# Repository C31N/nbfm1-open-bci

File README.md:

<!-- SPDX-License-Identifier: AGPL-3.0-only -->
# NBFM-1 Open BCI Stack

\n

Open-source research platform for a multimodal, non-invasive brain-computer interface built around three independently useful layers:

1. **NBFM-1** — an asynchronous neural foundation model with a millisecond-scale EEG/MEG fast path and a slower fNIRS context path.
2. **P1/P2 edge stack** — local inference, TensorRT/ONNX deployment, CUDA Graph-compatible I/O, encrypted local transport, intent gating, privacy zeroization, telemetry and systemd services.
3. **EEG128-TDM** — an ultra-low-cost 128-channel differential EEG acquisition architecture using paired 16:1 analog multiplexers, an 8-channel simultaneous-sampling delta-sigma ADC and an RP2040-class controller.

> **Research use only.** This repository does not claim medical-device certification, diagnostic suitability, prosthesis safety certification or validated free-form thought decoding. The project owner reports an existing external demonstration of multimodal measurement latency below 5 ms. The external report's raw samples and measurement conditions have not been imported into this checkout; preserve its actual measurement boundary when incorporating it. See [measurement scope and executable reference pipeline](docs/NEURAL_PIPELINE.md).

## Defensive publication

The enabling technical disclosure is in [`PATENT_DISCLOSURE.md`](PATENT_DISCLOSURE.md). The document is intentionally explicit about timing, packet formats, signal routing, filter-settling handling, asynchronous multimodal fusion and privacy gating so the disclosed combinations can be independently implemented and searched as public technical literature.

A repository commit is evidence, not magic. For a stronger publication record, publish a signed release, generate the repository SHA-256 manifest and archive that release in a DOI-backed repository such as Zenodo. See [`docs/PUBLICATION_PROCEDURE.md`](docs/PUBLICATION_PROCEDURE.md).

## System architecture

```mermaid
flowchart LR
    EEG["128-ch EEG<br/>1 kHz after decimation"] --> FAST["Fast neural path"]
    MEG["OPM-MEG<br/>geometry embeddings"] --> FAST
    FNIRS["fNIRS<br/>20 Hz short/long separation"] --> SLOW["Slow context encoder"]
    FAST --> NBFM["NBFM-1 causal transformer"]
    SLOW --> XATTN["Cross-attention"]
    XATTN --> NBFM
    NBFM --> MOTOR["Motor Gaussian head<br/>mu + sigma"]
    NBFM --> GATE["Intent gate<br/>P(intent)"]
    NBFM --> CTC["Phonemic CTC head"]
    GATE --> PRIVACY["Local-first privacy gate"]
    CTC --> PRIVACY
    PRIVACY --> ENC["AES-256-GCM local export"]
    MOTOR --> SAFETY["Rate/uncertainty limiter"]
    ENC --> AGENT["Local agent adapter"]
    SAFETY --> ACT["Cursor / bench actuator interface"]
```

### EEG128-TDM acquisition path

```mermaid
flowchart LR
    E["128 differential EEG channels<br/>256 electrode conductors"] --> M["8 banks x paired 16:1 MUX<br/>16 CD74HC4067 total"]
    M --> B["16 low-noise unity buffers"]
    B --> A["ADS131M08<br/>8 simultaneous 24-bit delta-sigma channels<br/>32 kSPS"]
    A --> R["RP2040<br/>SPI + DMA"]
    R --> D["16-position demultiplex<br/>settling discard + averaging"]
    D --> O["128 channels x 250 SPS<br/>offset/gain correction"]
```

## Hardware revision status

The repository contains **EEG128-TDM Revision A0** KiCad/BOM/CPL/netlist sources, but A0 is **not released for fabrication or human-connected use**. The board still requires independent routing and footprint verification followed by clean KiCad 8 ERC/DRC and the safety release gates in [`docs/SAFETY_COMPLIANCE.md`](docs/SAFETY_COMPLIANCE.md).

The manufacturing exporter is fail-closed: [`hardware/eeg128-tdm/generate_manufacturing.py`](hardware/eeg128-tdm/generate_manufacturing.py) refuses to generate Gerber output while [`RELEASE_STATUS.json`](hardware/eeg128-tdm/RELEASE_STATUS.json) contains an unmet release gate.

## Privacy-state machine

```text
LOCKED --explicit local arm--> ARMED --P(intent) >= T_gate--> DECODING
   ^                          |                              |
   |                          +--below threshold------------+
   +---------------- timeout / lock / fault ----------------+
```

Speech logits remain local. When the gate is closed, the export tensor is replaced with a fixed-shape zero tensor before encryption. Frame dimensions therefore do not reveal whether a private speech hypothesis existed.

## Physical hardware release status

The repository contains the A0 KiCad project, logical netlist, BOM/CPL and fail-closed manufacturing tooling, but **A0 is not released for fabrication or human-connected use**.

The current audited EDA state has placement/net assignments but not completed copper routing, and the current schematic is a connectivity index rather than a complete instantiated circuit schematic. The authoritative release blockers are machine-readable in `hardware/eeg128-tdm/RELEASE_STATUS.json`.

Run:

```bash
python3 hardware/eeg128-tdm/validate_eda.py
```

Manufacturing export remains blocked until the independent physical release gates are satisfied.

See:

- `hardware/eeg128-tdm/EDA_AUDIT.md`
- `docs/SAFETY_COMPLIANCE.md`
- `docs/AUDIT_2026-10-05.md`

## Quick start

```bash
chmod +x deploy_bci_stack.sh
./deploy_bci_stack.sh
```

Run the latency auditor after inference and bridge services are healthy:

```bash
python3 bin/audit_latency.py \
  --json reports/latency-audit.json \
  --html reports/latency-audit.html
```

A new benchmark passes only when its measured P99 meets the configured threshold.
The external result reported by the owner and a new revision's local compute
benchmark have separate evidence records. `bin/verify_latency_evidence.py` can
recompute an imported report without changing its stated measurement boundary.

The [reference pipeline guide](docs/NEURAL_PIPELINE.md) includes native LSL
ingestion, Python/Rust bounded rings, causal filtering, MAE/ridge interfaces and
AES-256-GCM session handling. The [143-airwire routing plan](hardware/eeg128-tdm/ROUTING_COMPLETION_143.md)
defines the remaining hardware work and the manufacturing prohibition.

## Licensing

Hardware design source and firmware are licensed under **CERN Open Hardware Licence Version 2 — Strongly Reciprocal (`CERN-OHL-S-2.0`)**. The NBFM-1 software architecture, inference stack, privacy gate, deployment code, scripts and project documentation are licensed under **GNU Affero General Public License v3.0 only (`AGPL-3.0-only`)**.

## Citation

Machine-readable citation metadata is in [`CITATION.cff`](CITATION.cff).

## Security

Neural raw data, derived embeddings, decoded speech, session keys, model weights and device-specific calibration can be sensitive. Never commit them. See [`SECURITY.md`](SECURITY.md) and the enforced exclusions in [`.gitignore`](.gitignore).

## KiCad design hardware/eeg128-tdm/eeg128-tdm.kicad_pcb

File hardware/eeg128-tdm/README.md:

<!-- SPDX-License-Identifier: CERN-OHL-S-2.0 -->
# EEG128-TDM Hardware Source — Revision A0

## Architecture

```text
128 differential logical EEG channels
= 256 subject/electrode conductors
        |
        v
8 banks x 16 logical channels
        |
        v
16 paired CD74HC4067-class 16:1 multiplexers
        |
        v
16 TLV9064-class unity buffers
        |
        v
ADS131M08-class 8-channel simultaneous delta-sigma ADC
32 kSPS, external 8.192-MHz clock
        |
        v
RP2040 SPI1 + DMA
        |
        v
4 post-switch conversions discarded
4 late conversions averaged
        |
        v
128 logical channels x 250 SPS
```

## Source files

| File | Purpose |
|---|---|
| `design_spec.yaml` | Human-readable electrical/stack-up source of truth |
| `NETLIST.csv` | Detailed endpoint-to-endpoint logical connectivity |
| `BOM.csv` | JLCPCB/LCSC-oriented bill of materials |
| `CPL.csv` | JLCPCB-oriented component placement |
| `eeg128-tdm.kicad_sch` | KiCad 8 schematic/connectivity index |
| `generate_schematic.py` | Deterministically generates a 642-component KiCad connectivity schematic from PCB pad/net assignments |
| `eeg128-tdm.kicad_pcb` | KiCad 8 four-layer A0 placement/net board |
| `eeg128-tdm.kicad_pro` | KiCad project |
| `validate_eda.py` | Source/BOM/CPL/net validation |
| `generate_manufacturing.py` | Fail-closed KiCad 8 ERC/DRC/Gerber/JLCPCB export |
| `RELEASE_STATUS.json` | Machine-readable fabrication/human-use release gates |

## Current fabrication status

**Revision A0 is not released for fabrication.**

The board source currently contains 642 component placements and logical pad-to-net assignments for A0 design review, but the copper routing is not complete, the KiCad schematic remains a generated connectivity representation rather than a manufacturer-symbol/pin-type reviewed circuit schematic, and generated footprint land patterns have not been independently verified. `RELEASE_STATUS.json` therefore keeps `fabrication_release=false`.

This is intentional. A large human-connected mixed-signal board must not become orderable merely because source files exist.

The manufacturing exporter refuses to run until all release gates are true.

## Validation

Repository-level structural validation:

```bash
python3 hardware/eeg128-tdm/validate_eda.py
```

Release validation additionally requires KiCad CLI 8:

```bash
cd hardware/eeg128-tdm
python3 validate_eda.py --kicad-release-checks
```

After independent routing/footprint/safety review and only after `RELEASE_STATUS.json` is intentionally signed off:

```bash
python3 generate_manufacturing.py
```

The script executes KiCad ERC and PCB DRC before exporting Gerber, drill and position data. Any failed release gate or KiCad violation stops the export.

## Four-layer intent

```text
L1  F.Cu   analog inputs, MUX/buffer/ADC and short local digital routes
L2  In1.Cu continuous return plane; analog/digital domains managed by placement/current paths
L3  In2.Cu 3V3A / 3V3D / VCM distribution
L4  B.Cu   high-speed digital, USB and controller-side routing
```

Do not create arbitrary AGND/DGND moat cuts that force return currents to detour. Domain control is primarily by placement/routing, with the ground-domain connection deliberately reviewed at the ADC/power boundary.

## Safety

This is research hardware, not IEC 60601-certified equipment.

No human-connected use is authorized by this repository revision. Follow `docs/SAFETY_COMPLIANCE.md`. In particular, a subject-connected analog domain must not have an uncontrolled galvanic path to mains-referenced equipment.

## License

Hardware source is covered by `CERN-OHL-S-2.0`.

## Package and grounding audit

### ADS131M08IPBSR

Use the TI **PBS** mechanical drawing as the authoritative footprint reference. The package has a nominal 5 mm square body with 0.50 mm lead pitch and approximately 7 mm overall lead span. Distributor summaries can describe these dimensions differently; release review must use the manufacturer drawing.

### Ground plane

The current logical source uses separate `AGND` and `DGND` names while the intended PCB strategy calls for a continuous return plane. This conflict must be resolved before routing release. Do not introduce an arbitrary split-plane slot solely to preserve naming.

### Internal reference

The selected low-noise reference network must be reviewed explicitly before A0 fabrication. The present logical netlist records `ADC_REFIN` as unpopulated; for EEG noise optimization, provision for local REFIN filtering must be evaluated against TI guidance and the chosen converter mode.

See `EDA_AUDIT.md` and `RELEASE_STATUS.json`.

## Generated connectivity schematic

The deterministic generator can materialize every PCB/BOM component and every assigned pad net into a KiCad 8 schematic representation:

```bash
python3 generate_schematic.py
```

Default output:

```text
eeg128-tdm.generated.kicad_sch
```

It uses real component references and PCB pad numbers and emits local labeled wire stubs for assigned nets. It intentionally uses conservative generic passive-pin symbols. Therefore it is useful for reproducible connectivity review and schematic/PCB parity, but it does **not** replace manufacturer-symbol pin-type review, analog/power/reference design review, or independently establish fabrication readiness.

Only after review may it replace the primary schematic:

```bash
python3 generate_schematic.py --replace-primary
```

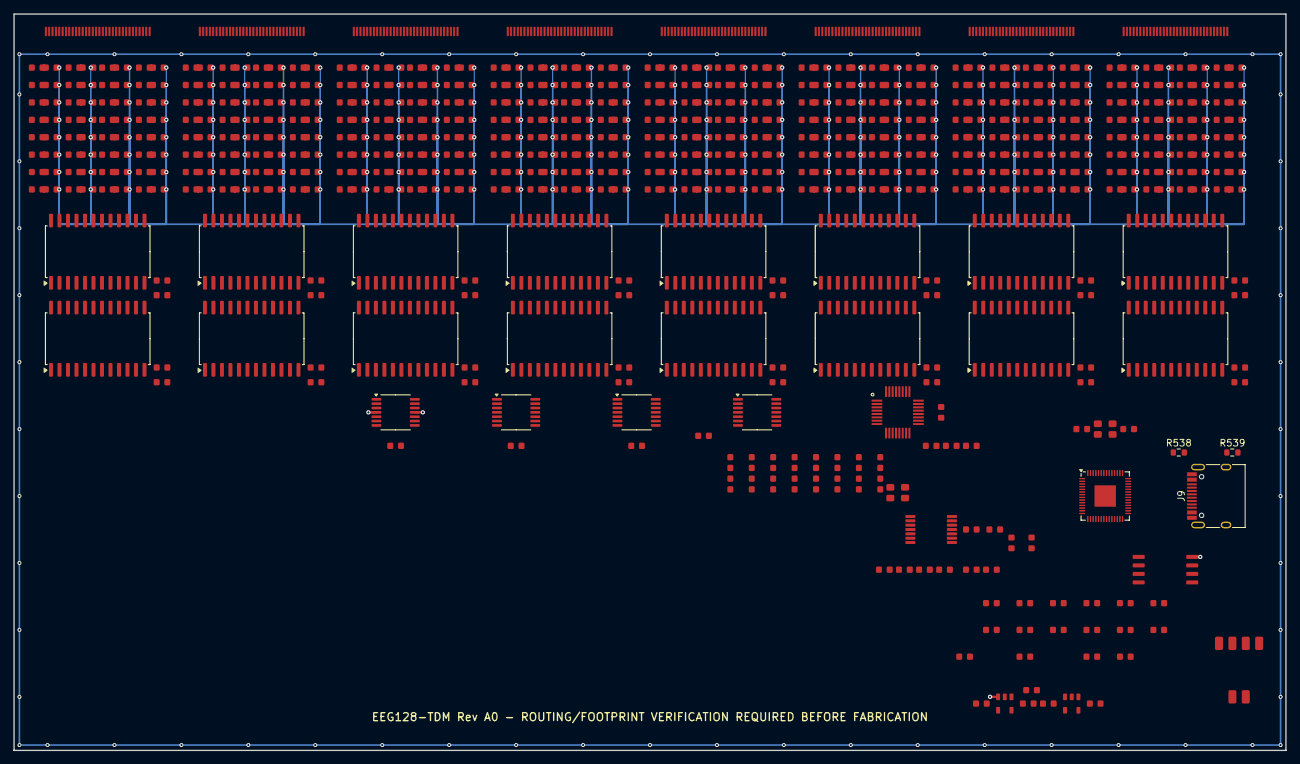
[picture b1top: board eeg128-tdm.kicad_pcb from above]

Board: 4 copper layers, 190.0 x 110.0 mm, 642 parts (0 on the bottom side), 604 nets.

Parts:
C1: C1
C2: C2
C3: C3
C4: C4
C5: C5
C6: C6
C7: C7
C8: C8
C9: C9
C10: C10
C11: C11
C12: C12
C13: C13
C14: C14
C15: C15
C16: C16
C17: C17
C18: C18
C19: C19
C20: C20
C21: C21
C22: C22
C23: C23
C24: C24
C25: C25
C26: C26
C27: C27
C28: C28
C29: C29
C30: C30
C31: C31
C32: C32
C33: C33
C34: C34
C35: C35
C36: C36
C37: C37
C38: C38
C39: C39
C40: C40
C41: C41
C42: C42
C43: C43
C44: C44
C45: C45
C46: C46
C47: C47
C48: C48
C49: C49
C50: C50
C51: C51
C52: C52
C53: C53
C54: C54
C55: C55
C56: C56
C57: C57
C58: C58
C59: C59
C60: C60
C61: C61
C62: C62
C63: C63
C64: C64
J1: J1
J2: J2
J3: J3
J4: J4
J5: J5
J6: J6
J7: J7
J8: J8
J9: TYPE-C-31-M-12; USB_C_Receptacle_HRO_TYPE-C-31-M-12
J10: J10
J11: J11
R1: R1
R2: R2
R3: R3
R4: R4
R5: R5
R6: R6
R7: R7
R8: R8
R9: R9
R10: R10
R11: R11
R12: R12
R13: R13
R14: R14
R15: R15
R16: R16
R17: R17
R18: R18
R19: R19
R20: R20
R21: R21
R22: R22
R23: R23
R24: R24
R25: R25
R26: R26
R27: R27
R28: R28
R29: R29
R30: R30
R31: R31
R32: R32
R33: R33
R34: R34
R35: R35
R36: R36
R37: R37
R38: R38
R39: R39
R40: R40
R41: R41
R42: R42
R43: R43
R44: R44
R45: R45
R46: R46
R47: R47
R48: R48
R49: R49
R50: R50
R51: R51
R52: R52
R53: R53
R54: R54
R55: R55
R56: R56
R57: R57
R58: R58
R59: R59
R60: R60
R61: R61
R62: R62
R63: R63
R64: R64
R65: R65
R66: R66
R67: R67
R68: R68
R69: R69
R70: R70
R71: R71
R72: R72
R73: R73
R74: R74
R75: R75
R76: R76
R77: R77
R78: R78
R79: R79
R80: R80
R81: R81
R82: R82
R83: R83
R84: R84
R85: R85
R86: R86
R87: R87
R88: R88
R89: R89
R90: R90
R91: R91
R92: R92
R93: R93
R94: R94
R95: R95
R96: R96
R97: R97
R98: R98
R99: R99
R100: R100
R101: R101
R102: R102
R103: R103
R104: R104
R105: R105
R106: R106
R107: R107
R108: R108
R109: R109
R110: R110
R111: R111
R112: R112
R113: R113
R114: R114
R115: R115
R116: R116
R117: R117
R118: R118
R119: R119
R120: R120
R121: R121
R122: R122
R123: R123
R124: R124
R125: R125
R126: R126
R127: R127
R128: R128
R129: R129
R130: R130
R131: R131
R132: R132
R133: R133
R134: R134
R135: R135
R136: R136
R137: R137
R138: R138
R139: R139
R140: R140
R141: R141
R142: R142
R143: R143
R144: R144
R145: R145
R146: R146
R147: R147
R148: R148
R149: R149
R150: R150
R151: R151
R152: R152
R153: R153
R154: R154
R155: R155
R156: R156
R157: R157
R158: R158
R159: R159
R160: R160
R161: R161
R162: R162
R163: R163
R164: R164
R165: R165
R166: R166
R167: R167
R168: R168
R169: R169
R170: R170
R171: R171
R172: R172
R173: R173
R174: R174
R175: R175
R176: R176
R177: R177
R178: R178
R179: R179
R180: R180
R181: R181
R182: R182
R183: R183
R184: R184
R185: R185
R186: R186
R187: R187
R188: R188
R189: R189
R190: R190
R191: R191
R192: R192
R193: R193
R194: R194
R195: R195
R196: R196
R197: R197
R198: R198
R199: R199
R200: R200
R201: R201
R202: R202
R203: R203
R204: R204
R205: R205
R206: R206
R207: R207
R208: R208
R209: R209
R210: R210
R211: R211
R212: R212
R213: R213
R214: R214
R215: R215
R216: R216
R217: R217
R218: R218
R219: R219
R220: R220
R221: R221
R222: R222
R223: R223
R224: R224
R225: R225
R226: R226
R227: R227
R228: R228
R229: R229
R230: R230
R231: R231
R232: R232
R233: R233
R234: R234
R235: R235
R236: R236
R237: R237
R238: R238
R239: R239
R240: R240
R241: R241
R242: R242
R243: R243
R244: R244
R245: R245
R246: R246
R247: R247
R248: R248
R249: R249
R250: R250
R251: R251
R252: R252
R253: R253
R254: R254
R255: R255
R256: R256
R257: R257
R258: R258
R259: R259
R260: R260
R261: R261
R262: R262
R263: R263
R264: R264
R265: R265
R266: R266
R267: R267
R268: R268
R269: R269
R270: R270
R271: R271
R272: R272
R273: R273
R274: R274
R275: R275
R276: R276
R277: R277
R278: R278
R279: R279
R280: R280
R281: R281
R282: R282
R283: R283
R284: R284
R285: R285
R286: R286
R287: R287
R288: R288
R289: R289
R290: R290
R291: R291
R292: R292
R293: R293
R294: R294
R295: R295
R296: R296
R297: R297
R298: R298
R299: R299
R300: R300
R301: R301
R302: R302
R303: R303
R304: R304
R305: R305
R306: R306
R307: R307
R308: R308
R309: R309
R310: R310
R311: R311
R312: R312
R313: R313
R314: R314
R315: R315
R316: R316
R317: R317
R318: R318
R319: R319
R320: R320
R321: R321
R322: R322
R323: R323
R324: R324
R325: R325
R326: R326
R327: R327
R328: R328
R329: R329
R330: R330
R331: R331
R332: R332
R333: R333
R334: R334
R335: R335
R336: R336
R337: R337
R338: R338
R339: R339
R340: R340
R341: R341
R342: R342
R343: R343
R344: R344
R345: R345
R346: R346
R347: R347
R348: R348
R349: R349
R350: R350
R351: R351
R352: R352
R353: R353
R354: R354
R355: R355
R356: R356
R357: R357
R358: R358
R359: R359
R360: R360
R361: R361
R362: R362
R363: R363
R364: R364
R365: R365
R366: R366
R367: R367
R368: R368
R369: R369
R370: R370
R371: R371
R372: R372
R373: R373
R374: R374
R375: R375
R376: R376
R377: R377
R378: R378
R379: R379
R380: R380
R381: R381
R382: R382
R383: R383
R384: R384
R385: R385
R386: R386
R387: R387
R388: R388
R389: R389
R390: R390
R391: R391
R392: R392
R393: R393
R394: R394
R395: R395
R396: R396
R397: R397
R398: R398
R399: R399
R400: R400
R401: R401
R402: R402
R403: R403
R404: R404
R405: R405
R406: R406
R407: R407
R408: R408
R409: R409
R410: R410
R411: R411
R412: R412
R413: R413
R414: R414
R415: R415
R416: R416
R417: R417
R418: R418
R419: R419
R420: R420
R421: R421
R422: R422
R423: R423
R424: R424
R425: R425
R426: R426
R427: R427
R428: R428
R429: R429
R430: R430
R431: R431
R432: R432
R433: R433
R434: R434
R435: R435
R436: R436
R437: R437
R438: R438
R439: R439
R440: R440
R441: R441
R442: R442
R443: R443
R444: R444
R445: R445
R446: R446
R447: R447
R448: R448
R449: R449
R450: R450
R451: R451
R452: R452
R453: R453
R454: R454
R455: R455
R456: R456
R457: R457
R458: R458
R459: R459
R460: R460
R461: R461
R462: R462
R463: R463
R464: R464
R465: R465
R466: R466
R467: R467
R468: R468
R469: R469
R470: R470
R471: R471
R472: R472
R473: R473
R474: R474
R475: R475
R476: R476
R477: R477
R478: R478
R479: R479
R480: R480
R481: R481
R482: R482
R483: R483
R484: R484
R485: R485
R486: R486
R487: R487
R488: R488
R489: R489
R490: R490
R491: R491
R492: R492
R493: R493
R494: R494
R495: R495
R496: R496
R497: R497
R498: R498
R499: R499
R500: R500
R501: R501
R502: R502
R503: R503
R504: R504
R505: R505
R506: R506
R507: R507
R508: R508
R509: R509
R510: R510
R511: R511
R512: R512
R513: R513
R514: R514
R515: R515
R516: R516
R517: R517
R518: R518
R519: R519
R520: R520
R521: R521
R522: R522
R523: R523
R524: R524
R525: R525
R526: R526
R527: R527
R528: R528
R529: R529
R530: R530
R531: R531
R532: R532
R533: R533
R534: R534
R535: R535
R536: R536
R537: R537
R538, R539: 5.1k; R_0603_1608Metric
U1: U1; SOIC-24W_7.5x15.4mm_P1.27mm
U2: U2; SOIC-24W_7.5x15.4mm_P1.27mm
U3: U3; SOIC-24W_7.5x15.4mm_P1.27mm
U4: U4; SOIC-24W_7.5x15.4mm_P1.27mm
U5: U5; SOIC-24W_7.5x15.4mm_P1.27mm
U6: U6; SOIC-24W_7.5x15.4mm_P1.27mm
U7: U7; SOIC-24W_7.5x15.4mm_P1.27mm
U8: U8; SOIC-24W_7.5x15.4mm_P1.27mm
U9: U9; SOIC-24W_7.5x15.4mm_P1.27mm
U10: U10; SOIC-24W_7.5x15.4mm_P1.27mm
U11: U11; SOIC-24W_7.5x15.4mm_P1.27mm
U12: U12; SOIC-24W_7.5x15.4mm_P1.27mm
U13: U13; SOIC-24W_7.5x15.4mm_P1.27mm
U14: U14; SOIC-24W_7.5x15.4mm_P1.27mm
U15: U15; SOIC-24W_7.5x15.4mm_P1.27mm
U16: U16; SOIC-24W_7.5x15.4mm_P1.27mm
U17: U17; TSSOP-14_4.4x5mm_P0.65mm
U18: U18; TSSOP-14_4.4x5mm_P0.65mm
U19: U19; TSSOP-14_4.4x5mm_P0.65mm
U20: U20; TSSOP-14_4.4x5mm_P0.65mm
U21: U21; TI_PBS_S-PQFP-G32_5x5mm_P0.5mm
U22: U22
U23: U23; QFN-56-1EP_7x7mm_P0.4mm_EP3.2x3.2mm
U24: U24
U25: U25
U26: U26
U27: U27
Y1: Y1

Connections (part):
3V3A: C1.1, C2.1, C3.1, C4.1, C5.1, C6.1, C7.1, C8.1, C9.1, C10.1, C11.1, C12.1, C13.1, C14.1, C15.1, C16.1, C18.1, C21.1, C22.1, C23.1, C24.1, C25.1, C26.1, C27.1, C28.1, C29.1, C30.1, C31.1, C32.1, C33.1, C34.1, C35.1, C36.1, C37.1, C38.1, C39.1, C40.1, C41.1, R529.1, U1.24, U2.24, U3.24, U4.24, U5.24, U6.24, U7.24, U8.24, U9.24, U10.24, U11.24, U12.24, U13.24, U14.24, U15.24, U16.24, U17.4, U18.4, U19.4, U20.4, U21.15, U22.4, U24.5
3V3D: C20.1, C42.1, C44.1, C45.1, C46.1, C47.1, C48.1, C49.1, C53.1, C54.1, C55.1, C56.1, C57.1, C58.1, C59.1, C60.1, U21.26, U23.1, U23.10, U23.22, U23.33, U23.42, U23.43, U23.44, U23.48, U23.49, U25.5, U26.8, U27.1, U27.4
5V_ISO: C17.1, C19.1, J9.A4, J9.A9, J9.B4, J9.B9, J11.1, U24.1, U24.3, U25.1, U25.3
ADC0_N: R514.2, U21.30
ADC0_P: R513.2, U21.29
ADC1_N: R516.2, U21.31
ADC1_P: R515.2, U21.32
ADC2_N: R518.2, U21.2
ADC2_P: R517.2, U21.1
ADC3_N: R520.2, U21.3
ADC3_P: R519.2, U21.4
ADC4_N: R522.2, U21.6
ADC4_P: R521.2, U21.5
ADC5_N: R524.2, U21.7
ADC5_P: R523.2, U21.8
ADC6_N: R526.2, U21.10
ADC6_P: R525.2, U21.9
ADC7_N: R528.2, U21.11
ADC7_P: R527.2, U21.12
ADC_CLKIN: U21.23, U27.3
ADC_CS: U21.17, U23.12
ADC_DIN: U21.21, U23.14
ADC_DOUT: U21.20, U23.11
ADC_DRDY: U21.18, U23.15
ADC_REFIN: C43.1, U21.14
ADC_SCLK: U21.19, U23.13
ADC_SYNC_RESET: U21.16, U23.16
ADS_CAP: C61.1, U21.24
AGND: C1.2, C2.2, C3.2, C4.2, C5.2, C6.2, C7.2, C8.2, C9.2, C10.2, C11.2, C12.2, C13.2, C14.2, C15.2, C16.2, C17.2, C18.2, C19.2, C20.2, C21.2, C22.2, C23.2, C24.2, C25.2, C26.2, C27.2, C28.2, C29.2, C30.2, C31.2, C32.2, C33.2, C34.2, C35.2, C36.2, C37.2, C38.2, C39.2, C40.2, C41.2, C42.2, C43.2, C44.2, C45.2, C46.2, C47.2, C48.2, C49.2, C50.2, C51.2, C52.2, C53.2, C54.2, C55.2, C56.2, C57.2, C58.2, C59.2, C60.2, C61.2, C63.2, C64.2, J9.A1, J9.A12, J9.B1, J9.B12, J11.2, R530.2, R538.2, R539.2, U1.12, U2.12, U3.12, U4.12, U5.12, U6.12, U7.12, U8.12, U9.12, U10.12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
BANK0_N_BUFFER: R514.1, U17.6, U17.7
BANK0_N_MUX_OUT: U2.1, U17.5
BANK0_P_BUFFER: R513.1, U17.1, U17.2
BANK0_P_MUX_OUT: U1.1, U17.3
BANK1_N_BUFFER: R516.1, U17.13, U17.14
BANK1_N_MUX_OUT: U4.1, U17.12
BANK1_P_BUFFER: R515.1, U17.8, U17.9
BANK1_P_MUX_OUT: U3.1, U17.10
BANK2_N_BUFFER: R518.1, U18.6, U18.7
BANK2_N_MUX_OUT: U6.1, U18.5
BANK2_P_BUFFER: R517.1, U18.1, U18.2
BANK2_P_MUX_OUT: U5.1, U18.3
BANK3_N_BUFFER: R520.1, U18.13, U18.14
BANK3_N_MUX_OUT: U8.1, U18.12
BANK3_P_BUFFER: R519.1, U18.8, U18.9
BANK3_P_MUX_OUT: U7.1, U18.10
BANK4_N_BUFFER: R522.1, U19.6, U19.7
BANK4_N_MUX_OUT: U10.1, U19.5
BANK4_P_BUFFER: R521.1, U19.1, U19.2
BANK4_P_MUX_OUT: U9.1, U19.3
BANK5_N_BUFFER: R524.1, U19.13, U19.14
BANK5_N_MUX_OUT: U12.1, U19.12
BANK5_P_BUFFER: R523.1, U19.8, U19.9
BANK5_P_MUX_OUT: U11.1, U19.10
BANK6_N_BUFFER: R526.1, U20.6, U20.7
BANK6_N_MUX_OUT: U14.1, U20.5
BANK6_P_BUFFER: R525.1, U20.1, U20.2
BANK6_P_MUX_OUT: U13.1, U20.3
BANK7_N_BUFFER: R528.1, U20.13, U20.14
BANK7_N_MUX_OUT: U16.1, U20.12
BANK7_P_BUFFER: R527.1, U20.8, U20.9
BANK7_P_MUX_OUT: U15.1, U20.10
CH000_N_ELECTRODE: J1.17, R258.1
CH000_N_MUX: R2.1, R258.2, U2.9
CH000_P_ELECTRODE: J1.1, R257.1
CH000_P_MUX: R1.1, R257.2, U1.9
CH001_N_ELECTRODE: J1.18, R260.1
CH001_N_MUX: R4.1, R260.2, U2.8
CH001_P_ELECTRODE: J1.2, R259.1
CH001_P_MUX: R3.1, R259.2, U1.8
CH002_N_ELECTRODE: J1.19, R262.1
CH002_N_MUX: R6.1, R262.2, U2.7
CH002_P_ELECTRODE: J1.3, R261.1
CH002_P_MUX: R5.1, R261.2, U1.7
CH003_N_ELECTRODE: J1.20, R264.1
CH003_N_MUX: R8.1, R264.2, U2.6
CH003_P_ELECTRODE: J1.4, R263.1
CH003_P_MUX: R7.1, R263.2, U1.6
CH004_N_ELECTRODE: J1.21, R266.1
CH004_N_MUX: R10.1, R266.2, U2.5
CH004_P_ELECTRODE: J1.5, R265.1
CH004_P_MUX: R9.1, R265.2, U1.5
CH005_N_ELECTRODE: J1.22, R268.1
CH005_N_MUX: R12.1, R268.2, U2.4
CH005_P_ELECTRODE: J1.6, R267.1
CH005_P_MUX: R11.1, R267.2, U1.4
CH006_N_ELECTRODE: J1.23, R270.1
CH006_N_MUX: R14.1, R270.2, U2.3
CH006_P_ELECTRODE: J1.7, R269.1
CH006_P_MUX: R13.1, R269.2, U1.3
CH007_N_ELECTRODE: J1.24, R272.1
CH007_N_MUX: R16.1, R272.2, U2.2
CH007_P_ELECTRODE: J1.8, R271.1
CH007_P_MUX: R15.1, R271.2, U1.2
CH008_N_ELECTRODE: J1.25, R274.1
CH008_N_MUX: R18.1, R274.2, U2.23
CH008_P_ELECTRODE: J1.9, R273.1
CH008_P_MUX: R17.1, R273.2, U1.23
CH009_N_ELECTRODE: J1.26, R276.1
CH009_N_MUX: R20.1, R276.2, U2.22
CH009_P_ELECTRODE: J1.10, R275.1
CH009_P_MUX: R19.1, R275.2, U1.22
CH010_N_ELECTRODE: J1.27, R278.1
CH010_N_MUX: R22.1, R278.2, U2.21
CH010_P_ELECTRODE: J1.11, R277.1
CH010_P_MUX: R21.1, R277.2, U1.21
CH011_N_ELECTRODE: J1.28, R280.1
CH011_N_MUX: R24.1, R280.2, U2.20
CH011_P_ELECTRODE: J1.12, R279.1
CH011_P_MUX: R23.1, R279.2, U1.20
CH012_N_ELECTRODE: J1.29, R282.1
CH012_N_MUX: R26.1, R282.2, U2.19
CH012_P_ELECTRODE: J1.13, R281.1
CH012_P_MUX: R25.1, R281.2, U1.19
CH013_N_ELECTRODE: J1.30, R284.1
CH013_N_MUX: R28.1, R284.2, U2.18
CH013_P_ELECTRODE: J1.14, R283.1
CH013_P_MUX: R27.1, R283.2, U1.18
CH014_N_ELECTRODE: J1.31, R286.1
CH014_N_MUX: R30.1, R286.2, U2.17
CH014_P_ELECTRODE: J1.15, R285.1
CH014_P_MUX: R29.1, R285.2, U1.17
CH015_N_ELECTRODE: J1.32, R288.1
CH015_N_MUX: R32.1, R288.2, U2.16
CH015_P_ELECTRODE: J1.16, R287.1
CH015_P_MUX: R31.1, R287.2, U1.16
CH016_N_ELECTRODE: J2.17, R290.1
CH016_N_MUX: R34.1, R290.2, U4.9
CH016_P_ELECTRODE: J2.1, R289.1
CH016_P_MUX: R33.1, R289.2, U3.9
CH017_N_ELECTRODE: J2.18, R292.1
CH017_N_MUX: R36.1, R292.2, U4.8
CH017_P_ELECTRODE: J2.2, R291.1
CH017_P_MUX: R35.1, R291.2, U3.8
CH018_N_ELECTRODE: J2.19, R294.1
CH018_N_MUX: R38.1, R294.2, U4.7
CH018_P_ELECTRODE: J2.3, R293.1
CH018_P_MUX: R37.1, R293.2, U3.7
CH019_N_ELECTRODE: J2.20, R296.1
CH019_N_MUX: R40.1, R296.2, U4.6
CH019_P_ELECTRODE: J2.4, R295.1
CH019_P_MUX: R39.1, R295.2, U3.6
CH020_N_ELECTRODE: J2.21, R298.1
CH020_N_MUX: R42.1, R298.2, U4.5
CH020_P_ELECTRODE: J2.5, R297.1
CH020_P_MUX: R41.1, R297.2, U3.5
CH021_N_ELECTRODE: J2.22, R300.1
CH021_N_MUX: R44.1, R300.2, U4.4
CH021_P_ELECTRODE: J2.6, R299.1
CH021_P_MUX: R43.1, R299.2, U3.4
CH022_N_ELECTRODE: J2.23, R302.1
CH022_N_MUX: R46.1, R302.2, U4.3
CH022_P_ELECTRODE: J2.7, R301.1
CH022_P_MUX: R45.1, R301.2, U3.3
CH023_N_ELECTRODE: J2.24, R304.1
CH023_N_MUX: R48.1, R304.2, U4.2
CH023_P_ELECTRODE: J2.8, R303.1
CH023_P_MUX: R47.1, R303.2, U3.2
CH024_N_ELECTRODE: J2.25, R306.1
CH024_N_MUX: R50.1, R306.2, U4.23
CH024_P_ELECTRODE: J2.9, R305.1
CH024_P_MUX: R49.1, R305.2, U3.23
CH025_N_ELECTRODE: J2.26, R308.1
CH025_N_MUX: R52.1, R308.2, U4.22
CH025_P_ELECTRODE: J2.10, R307.1
CH025_P_MUX: R51.1, R307.2, U3.22
CH026_N_ELECTRODE: J2.27, R310.1
CH026_N_MUX: R54.1, R310.2, U4.21
CH026_P_ELECTRODE: J2.11, R309.1
CH026_P_MUX: R53.1, R309.2, U3.21
CH027_N_ELECTRODE: J2.28, R312.1
CH027_N_MUX: R56.1, R312.2, U4.20
CH027_P_ELECTRODE: J2.12, R311.1
CH027_P_MUX: R55.1, R311.2, U3.20
CH028_N_ELECTRODE: J2.29, R314.1
CH028_N_MUX: R58.1, R314.2, U4.19
CH028_P_ELECTRODE: J2.13, R313.1
CH028_P_MUX: R57.1, R313.2, U3.19
CH029_N_ELECTRODE: J2.30, R316.1
CH029_N_MUX: R60.1, R316.2, U4.18
CH029_P_ELECTRODE: J2.14, R315.1
CH029_P_MUX: R59.1, R315.2, U3.18
CH030_N_ELECTRODE: J2.31, R318.1
CH030_N_MUX: R62.1, R318.2, U4.17
CH030_P_ELECTRODE: J2.15, R317.1
CH030_P_MUX: R61.1, R317.2, U3.17
CH031_N_ELECTRODE: J2.32, R320.1
CH031_N_MUX: R64.1, R320.2, U4.16
CH031_P_ELECTRODE: J2.16, R319.1
CH031_P_MUX: R63.1, R319.2, U3.16
CH032_N_ELECTRODE: J3.17, R322.1
CH032_N_MUX: R66.1, R322.2, U6.9
CH032_P_ELECTRODE: J3.1, R321.1
CH032_P_MUX: R65.1, R321.2, U5.9
CH033_N_ELECTRODE: J3.18, R324.1
CH033_N_MUX: R68.1, R324.2, U6.8
CH033_P_ELECTRODE: J3.2, R323.1
CH033_P_MUX: R67.1, R323.2, U5.8
CH034_N_ELECTRODE: J3.19, R326.1
CH034_N_MUX: R70.1, R326.2, U6.7
CH034_P_ELECTRODE: J3.3, R325.1
CH034_P_MUX: R69.1, R325.2, U5.7
CH035_N_ELECTRODE: J3.20, R328.1
CH035_N_MUX: R72.1, R328.2, U6.6
CH035_P_ELECTRODE: J3.4, R327.1
CH035_P_MUX: R71.1, R327.2, U5.6
CH036_N_ELECTRODE: J3.21, R330.1
CH036_N_MUX: R74.1, R330.2, U6.5
CH036_P_ELECTRODE: J3.5, R329.1
CH036_P_MUX: R73.1, R329.2, U5.5
CH037_N_ELECTRODE: J3.22, R332.1
CH037_N_MUX: R76.1, R332.2, U6.4
CH037_P_ELECTRODE: J3.6, R331.1
CH037_P_MUX: R75.1, R331.2, U5.4
CH038_N_ELECTRODE: J3.23, R334.1
CH038_N_MUX: R78.1, R334.2, U6.3
CH038_P_ELECTRODE: J3.7, R333.1
CH038_P_MUX: R77.1, R333.2, U5.3
CH039_N_ELECTRODE: J3.24, R336.1
CH039_N_MUX: R80.1, R336.2, U6.2
CH039_P_ELECTRODE: J3.8, R335.1
CH039_P_MUX: R79.1, R335.2, U5.2
CH040_N_ELECTRODE: J3.25, R338.1
CH040_N_MUX: R82.1, R338.2, U6.23
CH040_P_ELECTRODE: J3.9, R337.1
CH040_P_MUX: R81.1, R337.2, U5.23
CH041_N_ELECTRODE: J3.26, R340.1
CH041_N_MUX: R84.1, R340.2, U6.22
CH041_P_ELECTRODE: J3.10, R339.1
CH041_P_MUX: R83.1, R339.2, U5.22
CH042_N_ELECTRODE: J3.27, R342.1
CH042_N_MUX: R86.1, R342.2, U6.21
CH042_P_ELECTRODE: J3.11, R341.1
CH042_P_MUX: R85.1, R341.2, U5.21
CH043_N_ELECTRODE: J3.28, R344.1
CH043_N_MUX: R88.1, R344.2, U6.20
CH043_P_ELECTRODE: J3.12, R343.1
CH043_P_MUX: R87.1, R343.2, U5.20
CH044_N_ELECTRODE: J3.29, R346.1
CH044_N_MUX: R90.1, R346.2, U6.19
CH044_P_ELECTRODE: J3.13, R345.1
CH044_P_MUX: R89.1, R345.2, U5.19
CH045_N_ELECTRODE: J3.30, R348.1
CH045_N_MUX: R92.1, R348.2, U6.18
CH045_P_ELECTRODE: J3.14, R347.1
CH045_P_MUX: R91.1, R347.2, U5.18
CH046_N_ELECTRODE: J3.31, R350.1
CH046_N_MUX: R94.1, R350.2, U6.17
CH046_P_ELECTRODE: J3.15, R349.1
CH046_P_MUX: R93.1, R349.2, U5.17
CH047_N_ELECTRODE: J3.32, R352.1
CH047_N_MUX: R96.1, R352.2, U6.16
CH047_P_ELECTRODE: J3.16, R351.1
CH047_P_MUX: R95.1, R351.2, U5.16
CH048_N_ELECTRODE: J4.17, R354.1
CH048_N_MUX: R98.1, R354.2, U8.9
CH048_P_ELECTRODE: J4.1, R353.1
CH048_P_MUX: R97.1, R353.2, U7.9
CH049_N_ELECTRODE: J4.18, R356.1
CH049_N_MUX: R100.1, R356.2, U8.8
CH049_P_ELECTRODE: J4.2, R355.1
CH049_P_MUX: R99.1, R355.2, U7.8
CH050_N_ELECTRODE: J4.19, R358.1
CH050_N_MUX: R102.1, R358.2, U8.7
CH050_P_ELECTRODE: J4.3, R357.1
CH050_P_MUX: R101.1, R357.2, U7.7
CH051_N_ELECTRODE: J4.20, R360.1
CH051_N_MUX: R104.1, R360.2, U8.6
CH051_P_ELECTRODE: J4.4, R359.1
CH051_P_MUX: R103.1, R359.2, U7.6
CH052_N_ELECTRODE: J4.21, R362.1
CH052_N_MUX: R106.1, R362.2, U8.5
CH052_P_ELECTRODE: J4.5, R361.1
CH052_P_MUX: R105.1, R361.2, U7.5
CH053_N_ELECTRODE: J4.22, R364.1
CH053_N_MUX: R108.1, R364.2, U8.4
CH053_P_ELECTRODE: J4.6, R363.1
CH053_P_MUX: R107.1, R363.2, U7.4
CH054_N_ELECTRODE: J4.23, R366.1
CH054_N_MUX: R110.1, R366.2, U8.3
CH054_P_ELECTRODE: J4.7, R365.1
CH054_P_MUX: R109.1, R365.2, U7.3
CH055_N_ELECTRODE: J4.24, R368.1
CH055_N_MUX: R112.1, R368.2, U8.2
CH055_P_ELECTRODE: J4.8, R367.1
CH055_P_MUX: R111.1, R367.2, U7.2
CH056_N_ELECTRODE: J4.25, R370.1
CH056_N_MUX: R114.1, R370.2, U8.23
CH056_P_ELECTRODE: J4.9, R369.1
CH056_P_MUX: R113.1, R369.2, U7.23
CH057_N_ELECTRODE: J4.26, R372.1
CH057_N_MUX: R116.1, R372.2, U8.22
CH057_P_ELECTRODE: J4.10, R371.1
CH057_P_MUX: R115.1, R371.2, U7.22
CH058_N_ELECTRODE: J4.27, R374.1
CH058_N_MUX: R118.1, R374.2, U8.21
CH058_P_ELECTRODE: J4.11, R373.1
CH058_P_MUX: R117.1, R373.2, U7.21
CH059_N_ELECTRODE: J4.28, R376.1
CH059_N_MUX: R120.1, R376.2, U8.20
CH059_P_ELECTRODE: J4.12, R375.1
CH059_P_MUX: R119.1, R375.2, U7.20
CH060_N_ELECTRODE: J4.29, R378.1
CH060_N_MUX: R122.1, R378.2, U8.19
CH060_P_ELECTRODE: J4.13, R377.1
CH060_P_MUX: R121.1, R377.2, U7.19
CH061_N_ELECTRODE: J4.30, R380.1
CH061_N_MUX: R124.1, R380.2, U8.18
CH061_P_ELECTRODE: J4.14, R379.1
CH061_P_MUX: R123.1, R379.2, U7.18
CH062_N_ELECTRODE: J4.31, R382.1
CH062_N_MUX: R126.1, R382.2, U8.17
CH062_P_ELECTRODE: J4.15, R381.1
CH062_P_MUX: R125.1, R381.2, U7.17
CH063_N_ELECTRODE: J4.32, R384.1
CH063_N_MUX: R128.1, R384.2, U8.16
CH063_P_ELECTRODE: J4.16, R383.1
CH063_P_MUX: R127.1, R383.2, U7.16
CH064_N_ELECTRODE: J5.17, R386.1
CH064_N_MUX: R130.1, R386.2, U10.9
CH064_P_ELECTRODE: J5.1, R385.1
CH064_P_MUX: R129.1, R385.2, U9.9
CH065_N_ELECTRODE: J5.18, R388.1
CH065_N_MUX: R132.1, R388.2, U10.8
CH065_P_ELECTRODE: J5.2, R387.1
CH065_P_MUX: R131.1, R387.2, U9.8
CH066_N_ELECTRODE: J5.19, R390.1
CH066_N_MUX: R134.1, R390.2, U10.7
CH066_P_ELECTRODE: J5.3, R389.1
CH066_P_MUX: R133.1, R389.2, U9.7
CH067_N_ELECTRODE: J5.20, R392.1
CH067_N_MUX: R136.1, R392.2, U10.6
CH067_P_ELECTRODE: J5.4, R391.1
CH067_P_MUX: R135.1, R391.2, U9.6
CH068_N_ELECTRODE: J5.21, R394.1
CH068_N_MUX: R138.1, R394.2, U10.5
CH068_P_ELECTRODE: J5.5, R393.1
CH068_P_MUX: R137.1, R393.2, U9.5
CH069_N_ELECTRODE: J5.22, R396.1
CH069_N_MUX: R140.1, R396.2, U10.4
CH069_P_ELECTRODE: J5.6, R395.1
CH069_P_MUX: R139.1, R395.2, U9.4
CH070_N_ELECTRODE: J5.23, R398.1
CH070_N_MUX: R142.1, R398.2, U10.3
CH070_P_ELECTRODE: J5.7, R397.1
CH070_P_MUX: R141.1, R397.2, U9.3
CH071_N_ELECTRODE: J5.24, R400.1
CH071_N_MUX: R144.1, R400.2, U10.2
CH071_P_ELECTRODE: J5.8, R399.1
CH071_P_MUX: R143.1, R399.2, U9.2
CH072_N_ELECTRODE: J5.25, R402.1
CH072_N_MUX: R146.1, R402.2, U10.23
CH072_P_ELECTRODE: J5.9, R401.1
CH072_P_MUX: R145.1, R401.2, U9.23
CH073_N_ELECTRODE: J5.26, R404.1
CH073_N_MUX: R148.1, R404.2, U10.22
CH073_P_ELECTRODE: J5.10, R403.1
CH073_P_MUX: R147.1, R403.2, U9.22
CH074_N_ELECTRODE: J5.27, R406.1
CH074_N_MUX: R150.1, R406.2, U10.21
CH074_P_ELECTRODE: J5.11, R405.1
CH074_P_MUX: R149.1, R405.2, U9.21
CH075_N_ELECTRODE: J5.28, R408.1
CH075_N_MUX: R152.1, R408.2, U10.20
CH075_P_ELECTRODE: J5.12, R407.1
CH075_P_MUX: R151.1, R407.2, U9.20
CH076_N_ELECTRODE: J5.29, R410.1
CH076_N_MUX: R154.1, R410.2, U10.19
CH076_P_ELECTRODE: J5.13, R409.1
CH076_P_MUX: R153.1, R409.2, U9.19
CH077_N_ELECTRODE: J5.30, R412.1
CH077_N_MUX: R156.1, R412.2, U10.18
CH077_P_ELECTRODE: J5.14, R411.1
CH077_P_MUX: R155.1, R411.2, U9.18
CH078_N_ELECTRODE: J5.31, R414.1
CH078_N_MUX: R158.1, R414.2, U10.17
CH078_P_ELECTRODE: J5.15, R413.1
CH078_P_MUX: R157.1, R413.2, U9.17
CH079_N_ELECTRODE: J5.32, R416.1
CH079_N_MUX: R160.1, R416.2, U10.16
CH079_P_ELECTRODE: J5.16, R415.1
CH079_P_MUX: R159.1, R415.2, U9.16
CH080_N_ELECTRODE: J6.17, R418.1
CH080_N_MUX: R162.1, R418.2, U12.9
CH080_P_ELECTRODE: J6.1, R417.1
CH080_P_MUX: R161.1, R417.2, U11.9
CH081_N_ELECTRODE: J6.18, R420.1
CH081_N_MUX: R164.1, R420.2, U12.8
CH081_P_ELECTRODE: J6.2, R419.1
CH081_P_MUX: R163.1, R419.2, U11.8
CH082_N_ELECTRODE: J6.19, R422.1
CH082_N_MUX: R166.1, R422.2, U12.7
CH082_P_ELECTRODE: J6.3, R421.1
CH082_P_MUX: R165.1, R421.2, U11.7
CH083_N_ELECTRODE: J6.20, R424.1
CH083_N_MUX: R168.1, R424.2, U12.6
CH083_P_ELECTRODE: J6.4, R423.1
CH083_P_MUX: R167.1, R423.2, U11.6
CH084_N_ELECTRODE: J6.21, R426.1
CH084_N_MUX: R170.1, R426.2, U12.5
CH084_P_ELECTRODE: J6.5, R425.1
CH084_P_MUX: R169.1, R425.2, U11.5
CH085_N_ELECTRODE: J6.22, R428.1
CH085_N_MUX: R172.1, R428.2, U12.4
CH085_P_ELECTRODE: J6.6, R427.1
CH085_P_MUX: R171.1, R427.2, U11.4
CH086_N_ELECTRODE: J6.23, R430.1
CH086_N_MUX: R174.1, R430.2, U12.3
CH086_P_ELECTRODE: J6.7, R429.1
CH086_P_MUX: R173.1, R429.2, U11.3
CH087_N_ELECTRODE: J6.24, R432.1
CH087_N_MUX: R176.1, R432.2, U12.2
CH087_P_ELECTRODE: J6.8, R431.1
CH087_P_MUX: R175.1, R431.2, U11.2
CH088_N_ELECTRODE: J6.25, R434.1
CH088_N_MUX: R178.1, R434.2, U12.23
CH088_P_ELECTRODE: J6.9, R433.1
CH088_P_MUX: R177.1, R433.2, U11.23
CH089_N_ELECTRODE: J6.26, R436.1
CH089_N_MUX: R180.1, R436.2, U12.22
CH089_P_ELECTRODE: J6.10, R435.1
CH089_P_MUX: R179.1, R435.2, U11.22
CH090_N_ELECTRODE: J6.27, R438.1
CH090_N_MUX: R182.1, R438.2, U12.21
CH090_P_ELECTRODE: J6.11, R437.1
CH090_P_MUX: R181.1, R437.2, U11.21
CH091_N_ELECTRODE: J6.28, R440.1
CH091_N_MUX: R184.1, R440.2, U12.20
CH091_P_ELECTRODE: J6.12, R439.1
CH091_P_MUX: R183.1, R439.2, U11.20
CH092_N_ELECTRODE: J6.29, R442.1
CH092_N_MUX: R186.1, R442.2, U12.19
CH092_P_ELECTRODE: J6.13, R441.1
CH092_P_MUX: R185.1, R441.2, U11.19
CH093_N_ELECTRODE: J6.30, R444.1
CH093_N_MUX: R188.1, R444.2, U12.18
CH093_P_ELECTRODE: J6.14, R443.1
CH093_P_MUX: R187.1, R443.2, U11.18
CH094_N_ELECTRODE: J6.31, R446.1
CH094_N_MUX: R190.1, R446.2, U12.17
CH094_P_ELECTRODE: J6.15, R445.1
CH094_P_MUX: R189.1, R445.2, U11.17
CH095_N_ELECTRODE: J6.32, R448.1
CH095_N_MUX: R192.1, R448.2, U12.16
CH095_P_ELECTRODE: J6.16, R447.1
CH095_P_MUX: R191.1, R447.2, U11.16
CH096_N_ELECTRODE: J7.17, R450.1
CH096_N_MUX: R194.1, R450.2, U14.9
CH096_P_ELECTRODE: J7.1, R449.1
CH096_P_MUX: R193.1, R449.2, U13.9
CH097_N_ELECTRODE: J7.18, R452.1
CH097_N_MUX: R196.1, R452.2, U14.8
CH097_P_ELECTRODE: J7.2, R451.1
CH097_P_MUX: R195.1, R451.2, U13.8
CH098_N_ELECTRODE: J7.19, R454.1
CH098_N_MUX: R198.1, R454.2, U14.7
CH098_P_ELECTRODE: J7.3, R453.1
CH098_P_MUX: R197.1, R453.2, U13.7
CH099_N_ELECTRODE: J7.20, R456.1
CH099_N_MUX: R200.1, R456.2, U14.6
CH099_P_ELECTRODE: J7.4, R455.1
CH099_P_MUX: R199.1, R455.2, U13.6
CH100_N_ELECTRODE: J7.21, R458.1
CH100_N_MUX: R202.1, R458.2, U14.5
CH100_P_ELECTRODE: J7.5, R457.1
CH100_P_MUX: R201.1, R457.2, U13.5
CH101_N_ELECTRODE: J7.22, R460.1
CH101_N_MUX: R204.1, R460.2, U14.4
CH101_P_ELECTRODE: J7.6, R459.1
CH101_P_MUX: R203.1, R459.2, U13.4
CH102_N_ELECTRODE: J7.23, R462.1
CH102_N_MUX: R206.1, R462.2, U14.3
CH102_P_ELECTRODE: J7.7, R461.1
CH102_P_MUX: R205.1, R461.2, U13.3
CH103_N_ELECTRODE: J7.24, R464.1
CH103_N_MUX: R208.1, R464.2, U14.2
CH103_P_ELECTRODE: J7.8, R463.1
CH103_P_MUX: R207.1, R463.2, U13.2
CH104_N_ELECTRODE: J7.25, R466.1
CH104_N_MUX: R210.1, R466.2, U14.23
CH104_P_ELECTRODE: J7.9, R465.1
CH104_P_MUX: R209.1, R465.2, U13.23
CH105_N_ELECTRODE: J7.26, R468.1
CH105_N_MUX: R212.1, R468.2, U14.22
CH105_P_ELECTRODE: J7.10, R467.1
CH105_P_MUX: R211.1, R467.2, U13.22
CH106_N_ELECTRODE: J7.27, R470.1
CH106_N_MUX: R214.1, R470.2, U14.21
CH106_P_ELECTRODE: J7.11, R469.1
CH106_P_MUX: R213.1, R469.2, U13.21
CH107_N_ELECTRODE: J7.28, R472.1
CH107_N_MUX: R216.1, R472.2, U14.20
CH107_P_ELECTRODE: J7.12, R471.1
CH107_P_MUX: R215.1, R471.2, U13.20
CH108_N_ELECTRODE: J7.29, R474.1
CH108_N_MUX: R218.1, R474.2, U14.19
CH108_P_ELECTRODE: J7.13, R473.1
CH108_P_MUX: R217.1, R473.2, U13.19
CH109_N_ELECTRODE: J7.30, R476.1
CH109_N_MUX: R220.1, R476.2, U14.18
CH109_P_ELECTRODE: J7.14, R475.1
CH109_P_MUX: R219.1, R475.2, U13.18
CH110_N_ELECTRODE: J7.31, R478.1
CH110_N_MUX: R222.1, R478.2, U14.17
CH110_P_ELECTRODE: J7.15, R477.1
CH110_P_MUX: R221.1, R477.2, U13.17
CH111_N_ELECTRODE: J7.32, R480.1
CH111_N_MUX: R224.1, R480.2, U14.16
CH111_P_ELECTRODE: J7.16, R479.1
CH111_P_MUX: R223.1, R479.2, U13.16
CH112_N_ELECTRODE: J8.17, R482.1
CH112_N_MUX: R226.1, R482.2, U16.9
CH112_P_ELECTRODE: J8.1, R481.1
CH112_P_MUX: R225.1, R481.2, U15.9
CH113_N_ELECTRODE: J8.18, R484.1
CH113_N_MUX: R228.1, R484.2, U16.8
CH113_P_ELECTRODE: J8.2, R483.1
CH113_P_MUX: R227.1, R483.2, U15.8
CH114_N_ELECTRODE: J8.19, R486.1
CH114_N_MUX: R230.1, R486.2, U16.7
CH114_P_ELECTRODE: J8.3, R485.1
CH114_P_MUX: R229.1, R485.2, U15.7
CH115_N_ELECTRODE: J8.20, R488.1
CH115_N_MUX: R232.1, R488.2, U16.6
CH115_P_ELECTRODE: J8.4, R487.1
CH115_P_MUX: R231.1, R487.2, U15.6
CH116_N_ELECTRODE: J8.21, R490.1
CH116_N_MUX: R234.1, R490.2, U16.5
CH116_P_ELECTRODE: J8.5, R489.1
CH116_P_MUX: R233.1, R489.2, U15.5
CH117_N_ELECTRODE: J8.22, R492.1
CH117_N_MUX: R236.1, R492.2, U16.4
CH117_P_ELECTRODE: J8.6, R491.1
CH117_P_MUX: R235.1, R491.2, U15.4
CH118_N_ELECTRODE: J8.23, R494.1
CH118_N_MUX: R238.1, R494.2, U16.3
CH118_P_ELECTRODE: J8.7, R493.1
CH118_P_MUX: R237.1, R493.2, U15.3
CH119_N_ELECTRODE: J8.24, R496.1
CH119_N_MUX: R240.1, R496.2, U16.2
CH119_P_ELECTRODE: J8.8, R495.1
CH119_P_MUX: R239.1, R495.2, U15.2
CH120_N_ELECTRODE: J8.25, R498.1
CH120_N_MUX: R242.1, R498.2, U16.23
CH120_P_ELECTRODE: J8.9, R497.1
CH120_P_MUX: R241.1, R497.2, U15.23
CH121_N_ELECTRODE: J8.26, R500.1
CH121_N_MUX: R244.1, R500.2, U16.22
CH121_P_ELECTRODE: J8.10, R499.1
CH121_P_MUX: R243.1, R499.2, U15.22
CH122_N_ELECTRODE: J8.27, R502.1
CH122_N_MUX: R246.1, R502.2, U16.21
CH122_P_ELECTRODE: J8.11, R501.1
CH122_P_MUX: R245.1, R501.2, U15.21
CH123_N_ELECTRODE: J8.28, R504.1
CH123_N_MUX: R248.1, R504.2, U16.20
CH123_P_ELECTRODE: J8.12, R503.1
CH123_P_MUX: R247.1, R503.2, U15.20
CH124_N_ELECTRODE: J8.29, R506.1
CH124_N_MUX: R250.1, R506.2, U16.19
CH124_P_ELECTRODE: J8.13, R505.1
CH124_P_MUX: R249.1, R505.2, U15.19
CH125_N_ELECTRODE: J8.30, R508.1
CH125_N_MUX: R252.1, R508.2, U16.18
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
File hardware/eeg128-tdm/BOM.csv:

Comment,Designator,Footprint,LCSC Part #,Manufacturer,Manufacturer Part #,Qty
"16:1 analog multiplexer","U1,U2,U3,U4,U5,U6,U7,U8,U9,U10,U11,U12,U13,U14,U15,U16","SOIC-24_7.5x15.4mm_P1.27mm","C496123","Texas Instruments","CD74HC4067M96","16"
"Quad RRIO buffer","U17,U18,U19,U20","TSSOP-14_4.4x5mm_P0.65mm","C779410","Texas Instruments","TLV9064IPWR","4"
"8ch 24-bit delta-sigma ADC","U21","TQFP-32_5x5mm_P0.5mm","C2862610","Texas Instruments","ADS131M08IPBSR","1"
"Quad DRL/VCM op amp","U22","TSSOP-14_4.4x5mm_P0.65mm","C529553","Texas Instruments","OPA4171AIPWR","1"
"Microcontroller","U23","QFN-56-1EP_7x7mm_P0.4mm_EP3.2x3.2mm","C2040","Raspberry Pi","RP2040","1"
"Analog 3V3 LDO","U24","SOT-23-5","C2862740","Texas Instruments","TPS7A2033PDBVR","1"
"Digital 3V3 LDO","U25","SOT-23-5","C51118","Diodes Incorporated","AP2112K-3.3TRG1","1"
"16Mbit QSPI flash","U26","SOIC-8_5.3x5.3mm_P1.27mm","C82317","Winbond","W25Q16JVSSIQ","1"
"8.192MHz CMOS ADC clock","U27","SMD3225-4P","C7425393","YXC Crystal Oscillators","OT2JI-111-8.192M","1"
"32-pin 0.5mm FPC electrode bank","J1,J2,J3,J4,J5,J6,J7,J8","FPC_32P_P0.5mm_RA","C2919488","HDGC","0.5K-QX-32PWB","8"
"USB-C 16-pin receptacle","J9","USB-C-16P_RA","C165948","Korean Hroparts Elec","TYPE-C-31-M-12","1"
"CMS1/CMS2/DRL/SHIELD connector","J10","JST_PH_4P_RA_2.0mm","C265102","JST","S4B-PH-SM4-TB(LF)(SN)","1"
"Isolated 5V battery/data-domain input","J11","JST_PH_2P_RA_2.0mm","C295747","JST","S2B-PH-SM4-TB(LF)(SN)","1"
"12MHz RP2040 crystal","Y1","Crystal_SMD_3225-4Pin","C9002","YXC","X322512MSB4SI","1"
"10Mohm electrode bias","R1,R2,R3,R4,R5,R6,R7,R8,R9,R10,R11,R12,R13,R14,R15,R16,R17,R18,R19,R20,R21,R22,R23,R24,R25,R26,R27,R28,R29,R30,R31,R32,R33,R34,R35,R36,R37,R38,R39,R40,R41,R42,R43,R44,R45,R46,R47,R48,R49,R50,R51,R52,R53,R54,R55,R56,R57,R58,R59,R60,R61,R62,R63,R64,R65,R66,R67,R68,R69,R70,R71,R72,R73,R74,R75,R76,R77,R78,R79,R80,R81,R82,R83,R84,R85,R86,R87,R88,R89,R90,R91,R92,R93,R94,R95,R96,R97,R98,R99,R100,R101,R102,R103,R104,R105,R106,R107,R108,R109,R110,R111,R112,R113,R114,R115,R116,R117,R118,R119,R120,R121,R122,R123,R124,R125,R126,R127,R128,R129,R130,R131,R132,R133,R134,R135,R136,R137,R138,R139,R140,R141,R142,R143,R144,R145,R146,R147,R148,R149,R150,R151,R152,R153,R154,R155,R156,R157,R158,R159,R160,R161,R162,R163,R164,R165,R166,R167,R168,R169,R170,R171,R172,R173,R174,R175,R176,R177,R178,R179,R180,R181,R182,R183,R184,R185,R186,R187,R188,R189,R190,R191,R192,R193,R194,R195,R196,R197,R198,R199,R200,R201,R202,R203,R204,R205,R206,R207,R208,R209,R210,R211,R212,R213,R214,R215,R216,R217,R218,R219,R220,R221,R222,R223,R224,R225,R226,R227,R228,R229,R230,R231,R232,R233,R234,R235,R236,R237,R238,R239,R240,R241,R242,R243,R244,R245,R246,R247,R248,R249,R250,R251,R252,R253,R254,R255,R256","R_0603_1608Metric","C2092526","Vishay","RCS060310M0FKEA","256"
"100kohm electrode series protection","R257,R258,R259,R260,R261,R262,R263,R264,R265,R266,R267,R268,R269,R270,R271,R272,R273,R274,R275,R276,R277,R278,R279,R280,R281,R282,R283,R284,R285,R286,R287,R288,R289,R290,R291,R292,R293,R294,R295,R296,R297,R298,R299,R300,R301,R302,R303,R304,R305,R306,R307,R308,R309,R310,R311,R312,R313,R314,R315,R316,R317,R318,R319,R320,R321,R322,R323,R324,R325,R326,R327,R328,R329,R330,R331,R332,R333,R334,R335,R336,R337,R338,R339,R340,R341,R342,R343,R344,R345,R346,R347,R348,R349,R350,R351,R352,R353,R354,R355,R356,R357,R358,R359,R360,R361,R362,R363,R364,R365,R366,R367,R368,R369,R370,R371,R372,R373,R374,R375,R376,R377,R378,R379,R380,R381,R382,R383,R384,R385,R386,R387,R388,R389,R390,R391,R392,R393,R394,R395,R396,R397,R398,R399,R400,R401,R402,R403,R404,R405,R406,R407,R408,R409,R410,R411,R412,R413,R414,R415,R416,R417,R418,R419,R420,R421,R422,R423,R424,R425,R426,R427,R428,R429,R430,R431,R432,R433,R434,R435,R436,R437,R438,R439,R440,R441,R442,R443,R444,R445,R446,R447,R448,R449,R450,R451,R452,R453,R454,R455,R456,R457,R458,R459,R460,R461,R462,R463,R464,R465,R466,R467,R468,R469,R470,R471,R472,R473,R474,R475,R476,R477,R478,R479,R480,R481,R482,R483,R484,R485,R486,R487,R488,R489,R490,R491,R492,R493,R494,R495,R496,R497,R498,R499,R500,R501,R502,R503,R504,R505,R506,R507,R508,R509,R510,R511,R512","R_0603_1608Metric","C2989131","UNI-ROYAL","TC0325F1003T5F","256"
"100ohm ADC input isolation","R513,R514,R515,R516,R517,R518,R519,R520,R521,R522,R523,R524,R525,R526,R527,R528","R_0603_1608Metric","C22775","UNI-ROYAL","0603WAF1000T5E","16"
"10kohm VCM/CMS network","R529,R530,R531,R532","R_0603_1608Metric","C25804","UNI-ROYAL","0603WAF1002T5E","4"
"27ohm USB series","R533,R534","R_0603_1608Metric","C137753","Yageo","RC0603FR-0727RL","2"
"1Mohm DRL patient-current limit","R535,R536","R_0603_1608Metric","C105578","Yageo","RC0603FR-071ML","2"
"470kohm DRL feedback","R537","R_0603_1608Metric","C114622","Yageo","RC0603FR-07470KL","1"
"5.1kohm USB-C CC pulldown","R538,R539","R_0603_1608Metric","C23186","UNI-ROYAL","0603WAF5101T5E","2"
"1uF supply decoupling","C1,C2,C3,C4,C5,C6,C7,C8,C9,C10,C11,C12,C13,C14,C15,C16,C17,C18,C19,C20","C_0603_1608Metric","C15849","Samsung Electro-Mechanics","CL10A105KB8NNNC","20"
"100nF local decoupling","C21,C22,C23,C24,C25,C26,C27,C28,C29,C30,C31,C32,C33,C34,C35,C36,C37,C38,C39,C40,C41,C42,C43,C44,C45,C46,C47,C48,C49,C50,C51,C52,C53,C54,C55,C56,C57,C58,C59,C60","C_0603_1608Metric","C14663","Yageo","CC0603KRX7R9BB104","40"
"220nF ADS131M08 CAP bypass","C61","C_0603_1608Metric","C3894271","Samsung Electro-Mechanics","CL10B224KO8SFNC","1"
"10nF DRL compensation","C62","C_0603_1608Metric","C57112","FH","0603B103K500NT","1"
"15pF RP2040 crystal load","C63,C64","C_0603_1608Metric","C346207","Samsung Electro-Mechanics","CL10C150JB81PNC","2"

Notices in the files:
README.md:
Hardware License
https://img.shields.io/badge/software-AGPL--3.0--only-A42E2B
